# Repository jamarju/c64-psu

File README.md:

# C64 power supply unit

This is a compact and efficient 9VAC/5VDC power supply for the Commodore 64 with the following features:

* 230VAC input (but easy to modify for 115VAC operation).
* 5 VDC output, adjustable, 1.75A max.
* 9 VAC output, 1.67A max.
* 6.5 VDC overvoltage protection (latching).
* Low VDC output ripple (<25 mV<sub>pp</sub> @1A).
* 2A overcurrent protection.
* Low heat dissipation.
* Mains overvoltage and noise suppresion.

## Building, warnings and recommendations

The kicad-project/gerbers folder contains gerber files ready for production. These are my recommended PCB specifications:

* 1.6 mm PCB thickness
* 2 oz copper thickness
* Min track / clearance: 8 mil

Beware there are three SMD components with thermal pads on the base that can't be easily soldered with a regular iron. You'll need **solder paste and an oven or a heat gun for these**.

## 110VAC operation

To work at 110 VAC, do these modifications to the schematic:

1. Connect the two primaries of TR1 in parallel instead of series:

2. Replace RV3 (EPCOS 300 Vrms MOV) with EPCOS B72214S0151K101 (150 Vrms MOV).
3. Replace F3 (160 mA fuse) with 315 mA fuse.

## Adjusting 5VDC output

Start adjusting trimpot TP1 to get 5 VDC with no load.

Then check the voltage at the C64 input with the computer on. You should expect a bit less than 5V due to losses depending on the cable gauge and DIN connectors. Ideally you should aim at 5.0V but a bit of undervoltage (4.9V) appears to work okay on my C64 and will lower heat dissipation.

Output voltage can be adjusted in the [4.13V, 5.55V] range.

## Enclosure

STLs and Fusion 360 project included in the enclosure/ folder. Sorry FreeCAD, I tried to keep this opensource but bodies in 0.17 are just not mature enough and doing this in 0.16 was too painful.

### Printing recommendations

* The bottom side can be printed bottom side flat on the printer bed without support.
* The top cover can be printed top side flat on the bed with supports everywhere.
* Material: I recommend PETG because of its higher melting temperature, great mechanical properties and low warping.
* I do not recommend PLA because of its low melting temperature.
* I do not recomment ABS either because of its high contraction ratio (= corner warp).

For the enclosure, in addition to the BOM components, you'll need:

* 6 x [Female quick disconnect 4.8 mm terminals](https://www.aliexpress.com/item/Free-shipping-100pcs-lot-4-8-insert-the-plug-spring-sheathed-wire-terminal-connector-cold-pressed/32593657279.html)
* 6 x [PCB male quick disconnect (aka spade) 4.8mm terminals](https://www.aliexpress.com/item/100pcs-4-8-Inserts-Plug-Spring-Terminal-PCB-Solder-lug-type-thickness-0-8mm-two-legs/32707189841.html) (these can replace the ones on the BOM and are much cheaper)
* 1 x [M12 PG7 strain relief](https://www.aliexpress.com/item/10pcs-Waterproof-M16-PG9-M12-PG7-Cable-Connectors-Spiral-Strain-Relief-Protector/32923675313.html)
* 1 x [Panel mount AC socket + rocking switch + fuse](https://www.aliexpress.com/item/Power-Rocker-Switch-IEC-3-Pin-320-C14-Inlet-Power-Sockets-Switch-Connector-Plug-10A-250V/32802047471.html)
* 1 x [4 cores, 5 meters 20 AWG cable](https://www.aliexpress.com/item/20-AWG-0-5MM2-RVV-2-3-4-5-6-7-8-10-12-14-16/32921926304.html)
* 1 x [7 pin male DIN connector (5 pcs minimum order)](https://www.aliexpress.com/item/5pcs-DIN-male-Plug-Connector-7-Pin-with-Plastic-Handle/32386538198.html)
* 10 x [M3x8 hex head bolts (100 units minimum order)](https://www.aliexpress.com/store/product/Free-Shipping-100pcs-Lot-Metric-Thread-DIN912-M3x8-mm-M3-8-mm-304-Stainless-Steel-Hex/3094064_32851042824.html)
* 10 x [M3 nuts (100 units min order)](https://www.aliexpress.com/item/Free-shipping-100pcs-lot-Metric-thread-DIN934-M3-304-Stainless-Steel-Hex-Nuts/32405600179.html)

### Cable length

I recommend keeping the C64-side cable as short and thick as possible. I recommend 20 AWG, 1 meter long wires.

The expected loss over 1 meter of 20 AWG wire at 5VDC and 1A is 33 mV per leg or 67 mV round trip.

## Schematic and protective measures

This PSU uses a 9VAC, 30VA dual secondary (15 VA + 15 VA) transformer that provides up to 1.67 amps on each secondary.

The regulator is a TI LMR33630 switching DC/DC step down converter with a switching frequency ~400 KHz and a peak efficiency of 93%.

To prevent an overvoltage situation due to failure of the swithing regulator or the feedback network, a MAX6399 voltage supervisor is used to control a high side P-channel MOSFET at the input of the switcher. When an overvoltage condition (V<sub>out</sub> >6.5V) is detected, the MAX6399 pulls the gate of the MOSFET down and cuts the regulator input until the power is completely removed from the unit.

The MAX6399 also provides undervoltage protection for clean startup of the switcher.

In addition to the over/undervoltage supervisor 3 varistors (MOVs) provide surge protection on the primary and both secondaries and 3 fuses prevent prolonged overcurrent condition on both sides of the transformer. The switcher itself also has an instant overcurrent protection above 3A.

## Tests

### Output ripple

Test conditions: V<sub>out</sub>=5.1V, I<sub>out</sub>=1A.

* Low frequency ripple: <20mV<sub>pp</sub>

### Overvoltage protection

Overvoltage protection voltage threshold set at V<sub>out</sub> >= 6.53V via R1/R2 divider.

Test conditions: shorted feedback input of LMR33630 to GND during normal operation at V<sub>out</sub>=5.1V, I<sub>out</sub>=1A.

@ 100 us per division:

@ 10 us per division:

### Startup overshoot

Nominal V<sub>out</sub>: 5.10V
Overshoot: 5.36V (<10 ms)

### Power-ok and V<sub>out</sub> ramp-up

Undervoltage protection voltage threshold set at Vin <= 6.81V via R3/R4 divider.

* Yellow: V<sub>out</sub>
* Cyan: MAX6399 Power OK output (LMR33630 ENABLE input)

## TODO

* Actually test that this doesn't blow anything up. Tests should include at least:
  * Thermal behavior
  * Undervoltage POK (both edges)
  * Secondary-primary noise coupling
  * EMI emissions

## License

CC-BY-NC-SA (Attribution-NonCommercial-ShareAlike).

See LICENSE.txt for details.

Please do not mass (?) produce this without my permission.

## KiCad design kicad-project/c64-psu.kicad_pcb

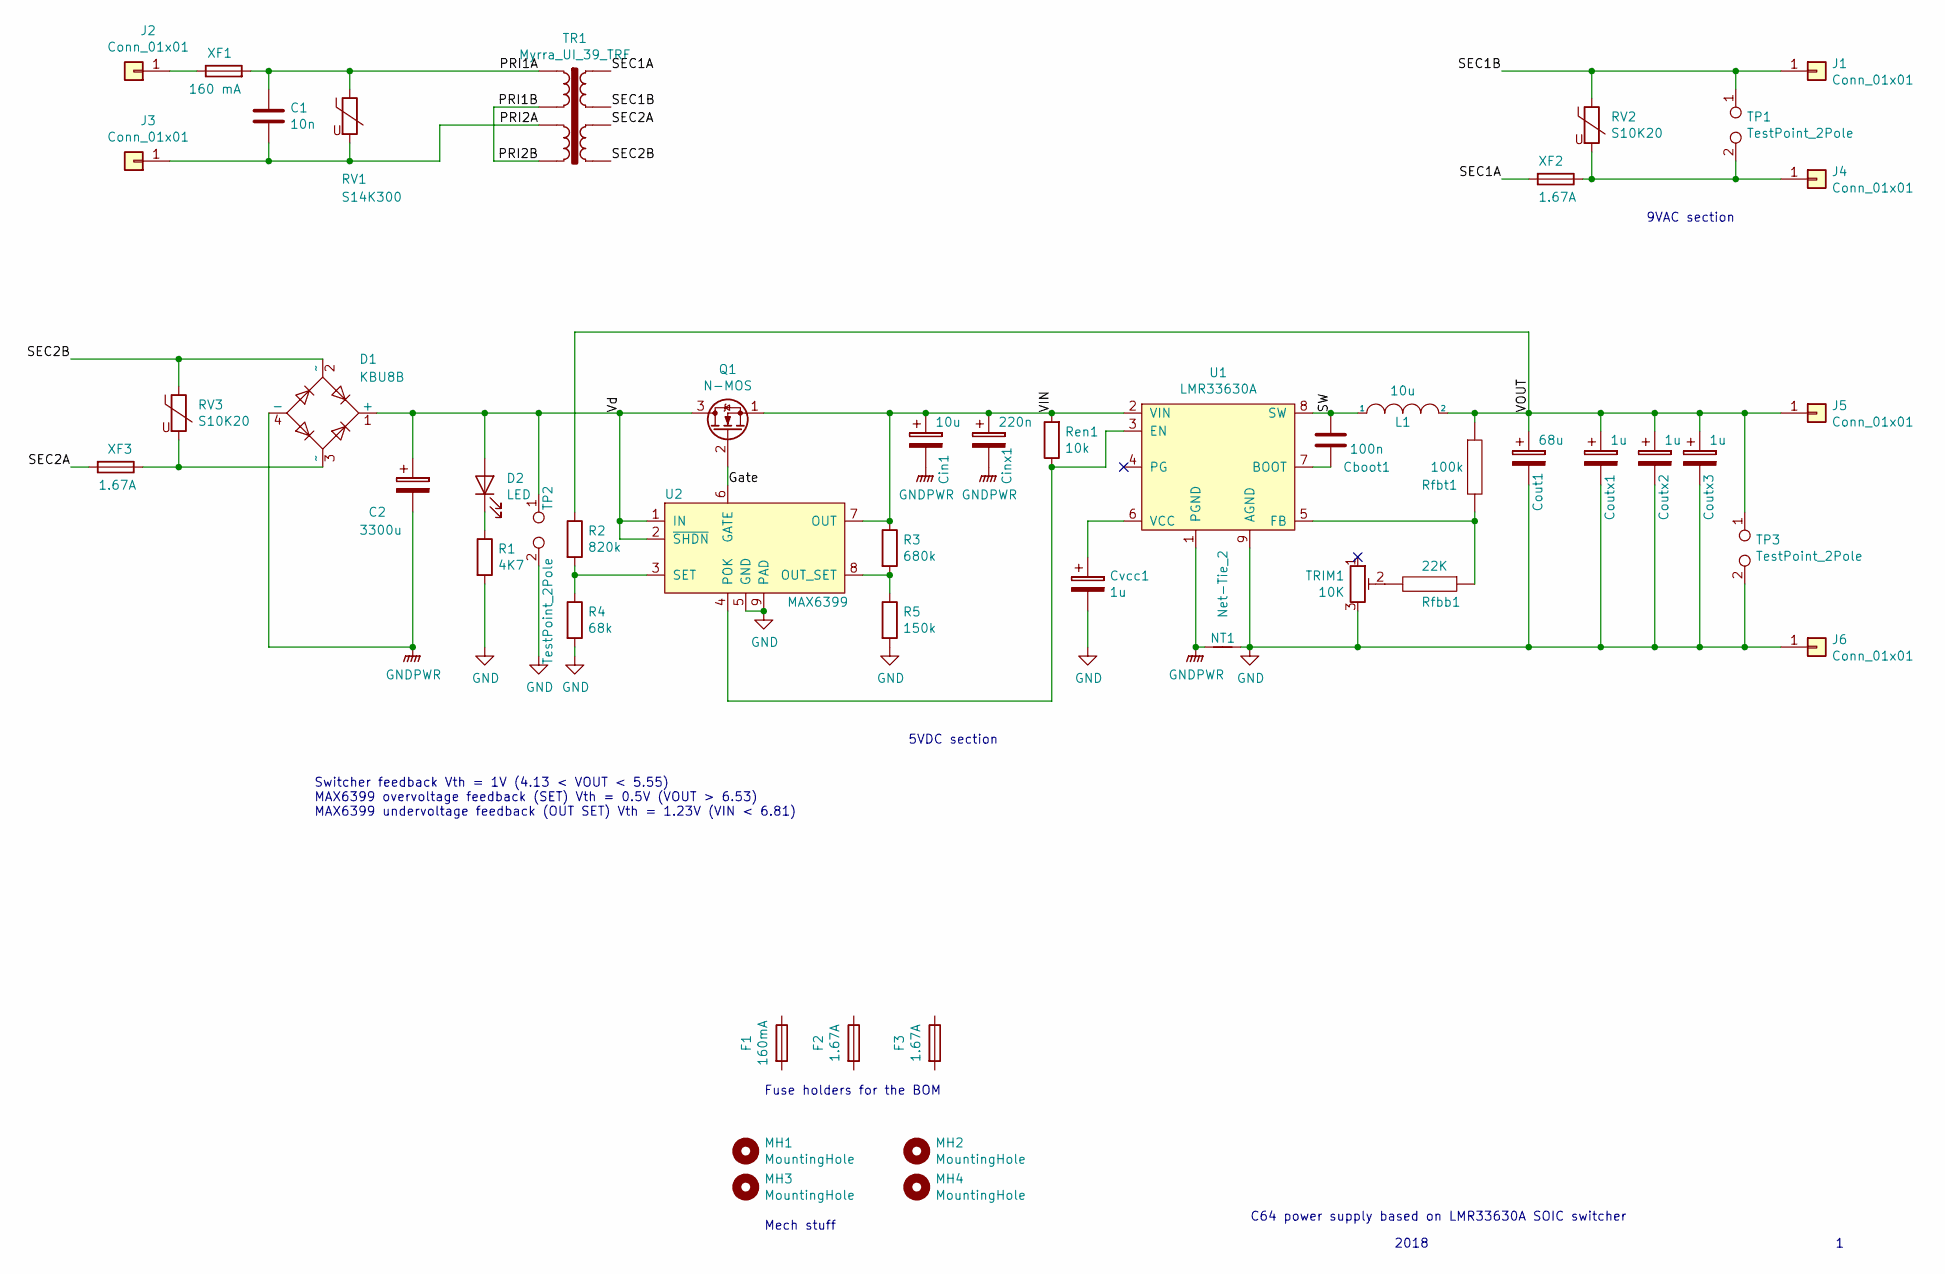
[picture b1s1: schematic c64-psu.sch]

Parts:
C1: 10n; C_Rect_L19.0mm_W5.0mm_P15.00mm_MKS4; MouserCode 80-R46KI21004001K1
C2: 3300u; CP_Radial_D18.0mm_P7.50mm; MouserCode 647-UHE1V332MHD6
Cboot1: 100n; C_0805_2012Metric_Pad1.15x1.40mm_HandSolder; MouserCode 603-CC805KRX7R9BB104
Cin1: 10u; C_1206_3216Metric_Pad1.42x1.75mm_HandSolder; MouserCode 810-C3216X6S1V106K6A
Cinx1: 220n; C_0805_2012Metric_Pad1.15x1.40mm_HandSolder; MouserCode 80-C0805C224K5RACTM
Cout1: 68u; C_1210_3225Metric_Pad1.42x2.65mm_HandSolder; MouserCode 810-C3225X5R0J686M
Coutx1, Coutx2, Coutx3: 1u; C_0805_2012Metric_Pad1.15x1.40mm_HandSolder; MouserCode 81-GRM40X105K10L
Cvcc1: 1u; C_0805_2012Metric_Pad1.15x1.40mm_HandSolder; MouserCode 80-C0805C105K8P
D1: KBU8B; Diode_Bridge_Vishay_KBU; MouserCode 905-KBU8B
D2: LED; LED_1206_3216Metric_Pad1.42x1.75mm_HandSolder
F1: 160mA; 20mm fuse; MouserCode 530-5ST160-R
F2, F3: 1.67A; 20mm fuse; MouserCode 530-5ST1.6-R
J1, J2, J3, J4, J5, J6: Conn_01x01; spade_4.8mm; MouserCode 534-1212-ST
L1: 10u; L_Bourns_SRR1260; MouserCode 652-SRR1260-100M
MH1, MH2, MH3, MH4: MountingHole; MountingHole_3.2mm_M3
NT1: Net-Tie_2; NetTie-2_THT_Pad1.0mm
Q1: N-MOS; LFPAK33-PSMN7R5-30MLD; MouserCode 771-PSMN7R5-30MLDX
R1: 4K7; R_1206_3216Metric_Pad1.42x1.75mm_HandSolder; MouserCode 652-CR1206FX-4701ELF
R2: 820k; R_0805_2012Metric_Pad1.15x1.40mm_HandSolder; MouserCode 652-CR0805FX-8203ELF
R3: 680k; R_0805_2012Metric_Pad1.15x1.40mm_HandSolder; MouserCode 652-CR0805FX-6803ELF
R4: 68k; R_0805_2012Metric_Pad1.15x1.40mm_HandSolder; MouserCode 652-CR0805FX-6802ELF
R5: 150k; R_0805_2012Metric_Pad1.15x1.40mm_HandSolder; MouserCode 652-CR0805FX-1503ELF
RV1: S14K300; RV_Disc_D15.5mm_W5.2mm_P7.5mm; MouserCode 871-B72214S301K101
RV2, RV3: S10K20; RV_Disc_D12mm_W4.5mm_P7.5mm; MouserCode 871-B72210S200K101
Ren1: 10k; R_0805_2012Metric_Pad1.15x1.40mm_HandSolder; MouserCode 652-CR0805FX-1002ELF
Rfbb1: 22K; R_0805_2012Metric_Pad1.15x1.40mm_HandSolder; MouserCode 652-CR0805-FX2202ELF
Rfbt1: 100k; R_0805_2012Metric_Pad1.15x1.40mm_HandSolder; MouserCode 652-CR0805FX-1003ELF
TP1, TP2, TP3: TestPoint_2Pole; TestPoint_2Pads_Pitch2.54mm_Drill0.8mm
TR1: Myrra_UI_39_TRF; Myrra UI 39 trf; FarnellCode 1777965
TRIM1: 10K; Potentiometer_Bourns_3296Y_Vertical; MouserCode 81-PV36Y103C01B00
U1: LMR33630A; TI_SO-PowerPAD-8_ThermalVias; MouserCode 595-LMR33630ADDAR
U2: MAX6399; DFN-8-1EP_3x3mm_P0.65mm_EP1.55x2.4mm; MouserCode 700-MAX6399ATAT
XF1: 160 mA; Fuseholder_Cylinder-5x20mm_Schurter_0031_8201_Horizontal_Op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; MouserCode 693-0031.8201
XF2, XF3: 1.67A; Fuseholder_Cylinder-5x20mm_Schurter_0031_8201_Horizontal_Op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; MouserCode 693-0031.8201

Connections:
/Gate: Q1.2 (G), U2.6 (GATE)
/PRI1A: C1.1, RV1.1, TR1.1, XF1.2
/PRI1B: TR1.4, TR1.9
/PRI2A: C1.2, J3.1, RV1.2, TR1.6
/SEC1A: TR1.19, XF2.2
/SEC1B: J1.1, RV2.1, TP1.1, TR1.17
/SEC2A: TR1.14, XF3.2
/SEC2B: D1.2 (~~), RV3.1, TR1.12
/SW: Cboot1.2, L1.1, U1.8 (SW)
/VIN: Cin1.1, Cinx1.1, Q1.1 (S), R3.1, Ren1.2, U1.2 (VIN), U2.7 (OUT)
/VOUT: Cout1.1, Coutx1.1, Coutx2.1, Coutx3.1, J5.1, L1.2, R2.1, Rfbt1.1, TP3.1
/Vd: C2.1, D1.1 (+), D2.2 (A), Q1.3 (D), TP2.1, U2.1 (IN), U2.2 (~SHDN)
GND: Cout1.2, Coutx1.2, Coutx2.2, Coutx3.2, Cvcc1.2, J6.1, NT1.2, R1.2, R4.2, R5.2, TP2.2, TP3.2, TRIM1.3, U1.9 (AGND), U2.5 (GND), U2.9 (PAD)
GNDPWR: C2.2, Cin1.2, Cinx1.2, D1.4 (-), NT1.1, U1.1 (PGND)
unnamed: Cboot1.1, U1.7 (BOOT)
unnamed: Cvcc1.1, U1.6 (VCC)
unnamed: D1.3 (~~), RV3.2, XF3.1
unnamed: D2.1 (K), R1.1
unnamed: J2.1, XF1.1
unnamed: J4.1, RV2.2, TP1.2, XF2.1
unnamed: R2.2, R4.1, U2.3 (SET)
unnamed: R3.2, R5.1, U2.8 (OUT_SET)
unnamed: Ren1.1, U1.3 (EN), U2.4 (POK)
unnamed: Rfbb1.1, Rfbt1.2, U1.5 (FB)
unnamed: Rfbb1.2, TRIM1.2

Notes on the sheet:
C64 power supply based on LMR33630A SOIC switcher
2018
Fuse holders for the BOM
Mech stuff
9VAC section
5VDC section
Switcher feedback Vth = 1V (4.13 < VOUT < 5.55) MAX6399 overvoltage feedback (SET) Vth = 0.5V (VOUT > 6.53) MAX6399 undervoltage feedback (OUT SET) Vth = 1.23V (VIN < 6.81)

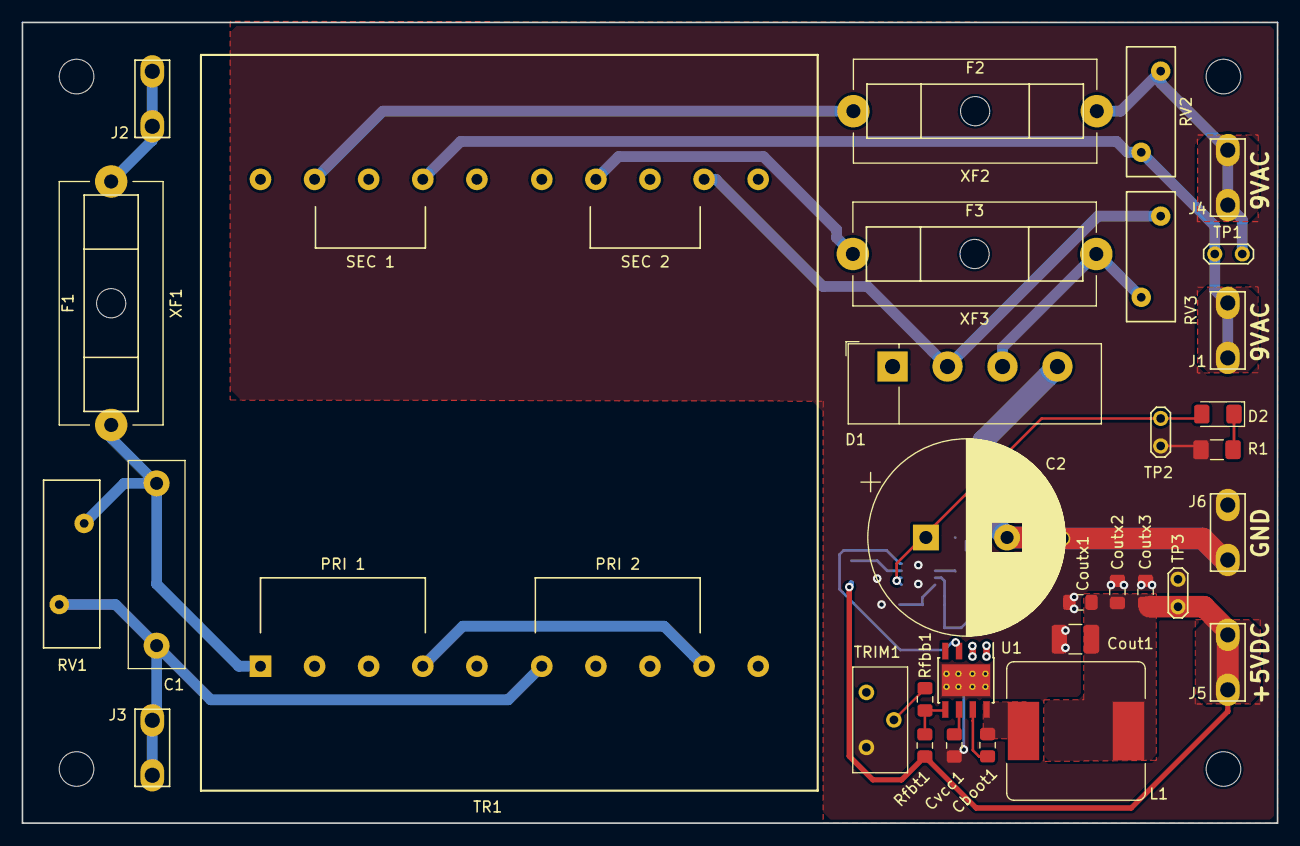
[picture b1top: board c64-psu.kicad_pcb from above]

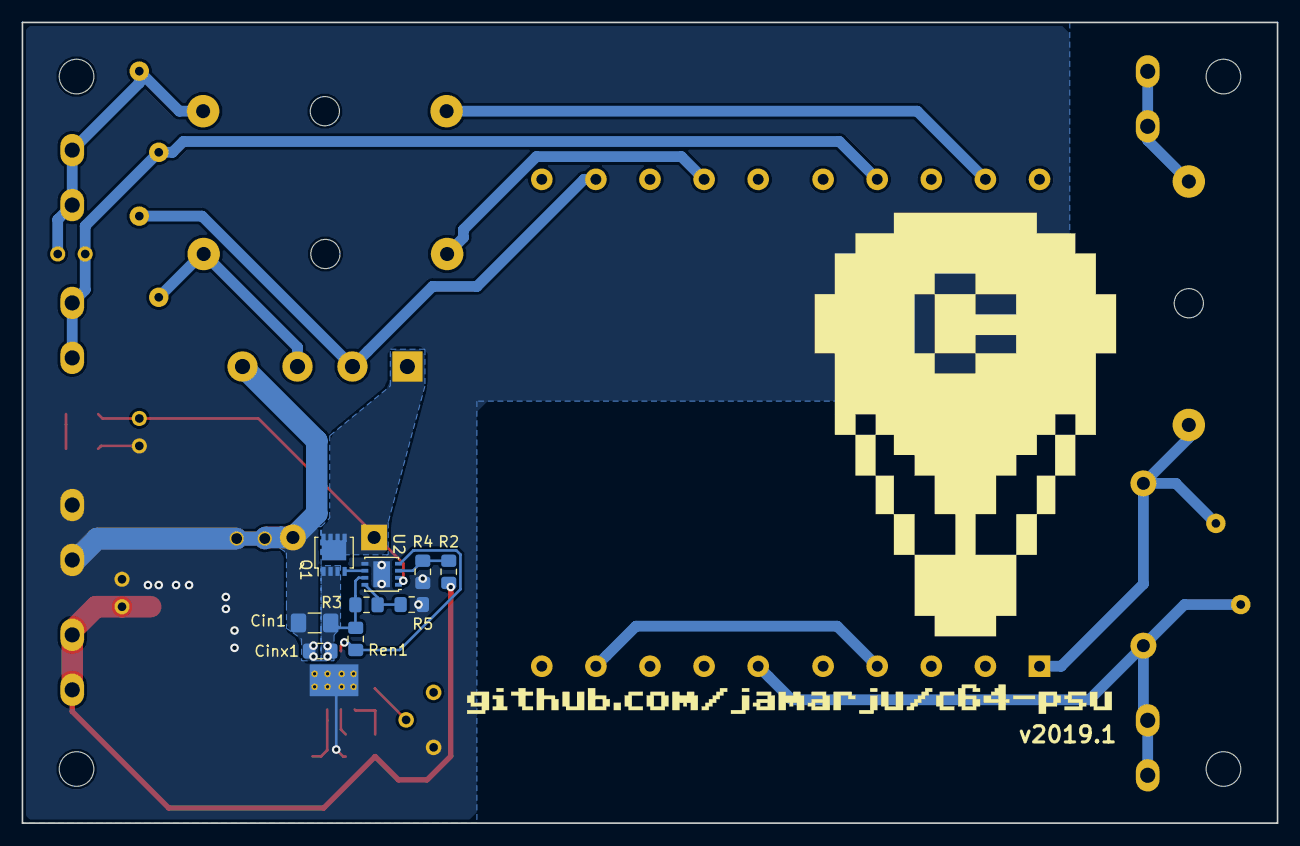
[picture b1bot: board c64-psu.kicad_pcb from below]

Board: 2 copper layers, 116.0 x 74.0 mm, 49 parts (9 on the bottom side), 25 nets.

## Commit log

2018-11-18 1st commit, untested design, lots of todos
2018-11-18 gitignore
2018-11-18 replace " with ' in BOM
2018-11-18 bom: manually remove mounting holes as their missing fields confuse github
2018-12-07 fix TR1 primary series connection (!!!), added voltage threshold comments on schematic, reversed J3 (when did that break?), added test captures,
2018-12-11 fix R5 value and MfrCode
    (was a 1206 10K but MfrCode was of a 0805 470 resistor). Also lowered original value of 10K to 4K7 to balance LED power waste vs overvoltage latch reset time
2018-12-24 HF noise improvements (reduce high di/dt loop area, reduce SW node area, etc.).
    Also:
    + Moved trf's origin to pin 1
    + Replaced 5 mm pitch connectors with (apparently safer) 7.62 mm
    ToDo:
    - Could be further improved by fitting the switcher between the filter cap legs on the bottom side! Will try that next.
2019-02-12 enclosure for v2018.1 (aka white PCB with trafo primary series bug)
2019-02-12 ignore docs (public datasheets)
2019-02-12 v2018.2 ready for mfr
    + replaced terminal blocks with quick-disconnect / spade connectors +
    + added footprints for fuses
    + enclosure redone in fusion 3d (sorry freecad 0.17 bodies are not mature yet, I tried)
    + gerbers ready for prod
2019-02-12 added enclosure STLs
2019-02-13 fixed bug: copper fill under spade connectors to prevent ground plane shorts
    gerbers + bom redone
2019-02-13 added license, enclosure render + additional parts links
2019-02-13 added schematic to the README
2019-02-14 added enclosure related BOM + caution on SMD soldering, cable length recommendations, etc.
